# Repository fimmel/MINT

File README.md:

# MINT Access Control System

This is the custom system for Access and tool control for the Rutland MINT makerspace. It uses standard HID readers, Arduinos, and a backend SQL database with a PHP webserver to manage users, permission, and cards.

There is lotsmore coming as well as an overview of how it all works

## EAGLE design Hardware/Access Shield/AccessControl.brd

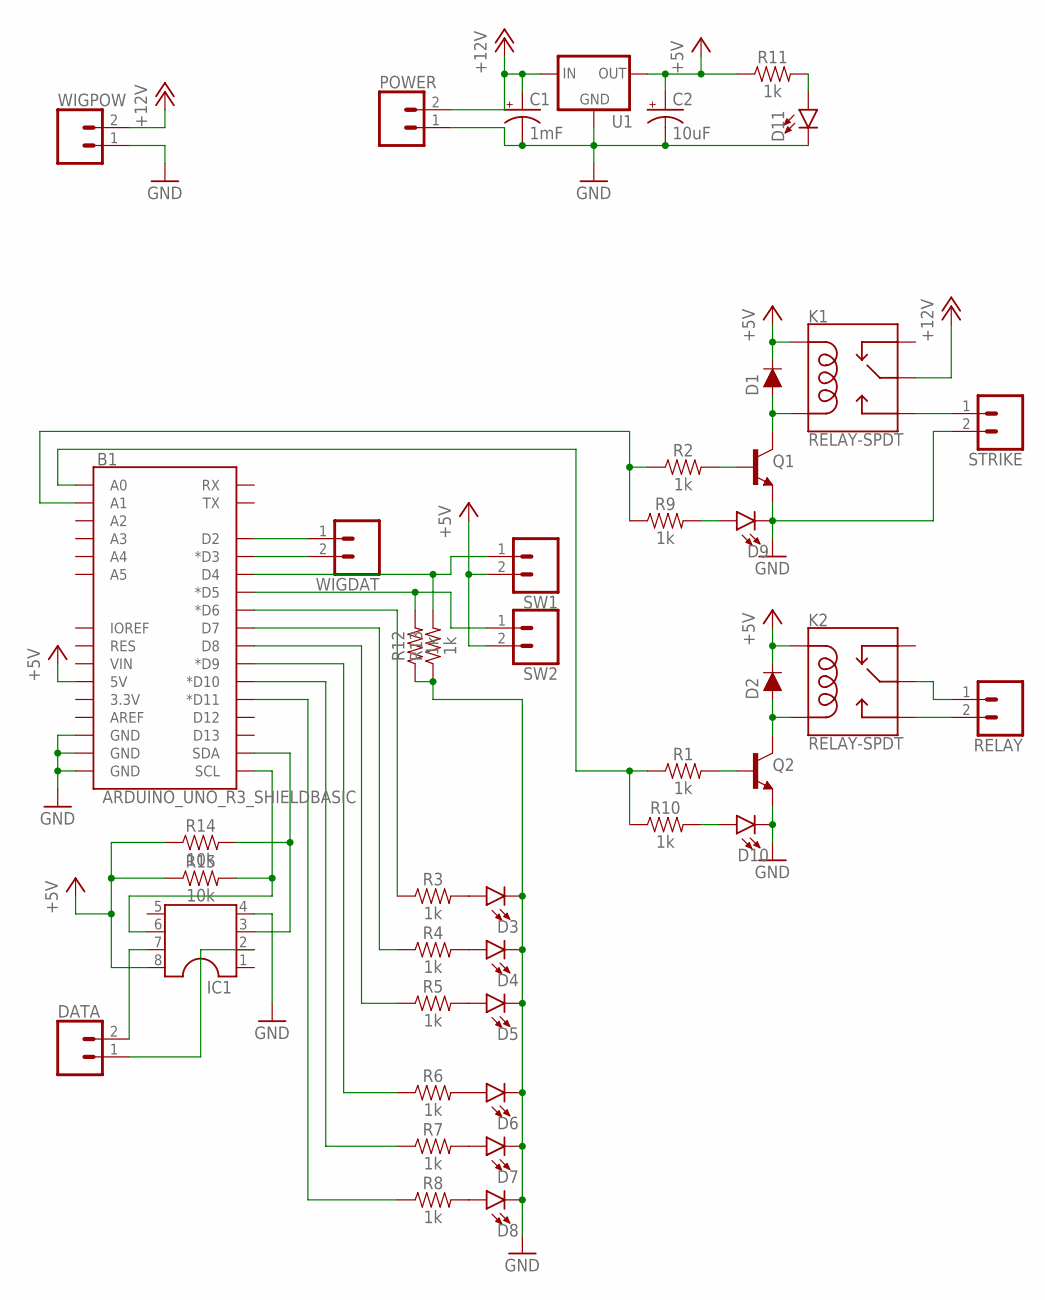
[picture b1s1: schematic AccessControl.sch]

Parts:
B1: ARDUINO_UNO_R3_SHIELDBASIC; UNO_R3_SHIELD
C1: 1mF; CPOL-RADIAL-5MM-10MM
C2: 10uF; CPOL-RADIAL-2.5MM-5MM
D1, D2: DIODE-KIT2; DIODE-1N4001-KIT
D3, D4, D5, D6, D7, D8, D9, D10, D11: LED5MM; LED_5MM
DATA: CONN_025MM; SCREWTERMINAL-5MM-2
IC1: DIL8; DIL08
K1, K2: RELAY-SPDT; RELAY-JZC
POWER: CONN_025MM; SCREWTERMINAL-5MM-2
Q1, Q2: TRANS_NPN-P2N2222A; TO-92
R1, R2, R3, R4, R5, R6, R7, R8, R9, R10, R11, R12, R13: 1k; AXIAL-0.1
R14, R15: 10k; AXIAL-0.1
RELAY: CONN_025MM; SCREWTERMINAL-5MM-2
STRIKE: CONN_025MM; SCREWTERMINAL-5MM-2
SW1, SW2: CONN_025MM; SCREWTERMINAL-5MM-2
U1: V_REG_78XXSINK; TO220-IGO
WIGDAT: CONN_025MM; SCREWTERMINAL-5MM-2
WIGPOW: CONN_025MM; SCREWTERMINAL-5MM-2

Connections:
+5V: B1.5V, C2.1 (+), D1.C, D2.C, IC1.8, K1.5 (COIL1), K2.5 (COIL1), R11.P$1 (1), R14.P$1 (1), R15.P$1 (1), SW1.2, SW2.2, U1.OUT
+12V: C1.+, K1.4 (MAIN), POWER.2, U1.IN, WIGPOW.2
GND: B1.GND@0 (GND), B1.GND@1 (GND), B1.GND@2 (GND), C1.-, C2.2 (-), D3.K (C), D4.K (C), D5.K (C), D6.K (C), D7.K (C), D8.K (C), D9.K (C), D10.K (C), D11.K (C), IC1.4, POWER.1, Q1.3 (E), Q2.3 (E), R12.P$1 (1), R13.P$1 (1), STRIKE.2, U1.GND, WIGPOW.1
unnamed: D1.A, K1.1 (COIL2), Q1.1 (C)
unnamed: Q1.2 (B), R2.P$2 (2)
unnamed: D2.A, K2.1 (COIL2), Q2.1 (C)
unnamed: Q2.2 (B), R1.P$2 (2)
unnamed: K2.3 (NO), RELAY.2
unnamed: K2.4 (MAIN), RELAY.1
unnamed: K1.3 (NO), STRIKE.1
unnamed: B1.D2, WIGDAT.1
unnamed: B1.D3 (*D3), WIGDAT.2
unnamed: B1.A0, R1.P$1 (1), R10.P$1 (1)
unnamed: B1.A1, R2.P$1 (1), R9.P$1 (1)
unnamed: D3.A, R3.P$2 (2)
unnamed: D4.A, R4.P$2 (2)
unnamed: D5.A, R5.P$2 (2)
unnamed: D6.A, R6.P$2 (2)
unnamed: D7.A, R7.P$2 (2)
unnamed: D8.A, R8.P$2 (2)
unnamed: D11.A, R11.P$2 (2)
unnamed: D9.A, R9.P$2 (2)
unnamed: D10.A, R10.P$2 (2)
unnamed: B1.D6 (*D6), R3.P$1 (1)
unnamed: B1.D7, R4.P$1 (1)
unnamed: B1.D8, R5.P$1 (1)
unnamed: B1.D9 (*D9), R6.P$1 (1)
unnamed: B1.D10 (*D10), R7.P$1 (1)
unnamed: B1.D11 (*D11), R8.P$1 (1)
unnamed: B1.SDA, IC1.3, R14.P$2 (2)
unnamed: B1.D4, R13.P$2 (2), SW1.1
unnamed: B1.D5 (*D5), R12.P$2 (2), SW2.1
unnamed: B1.SCL, IC1.6, R15.P$2 (2)
unnamed: DATA.2, IC1.7
unnamed: DATA.1, IC1.2

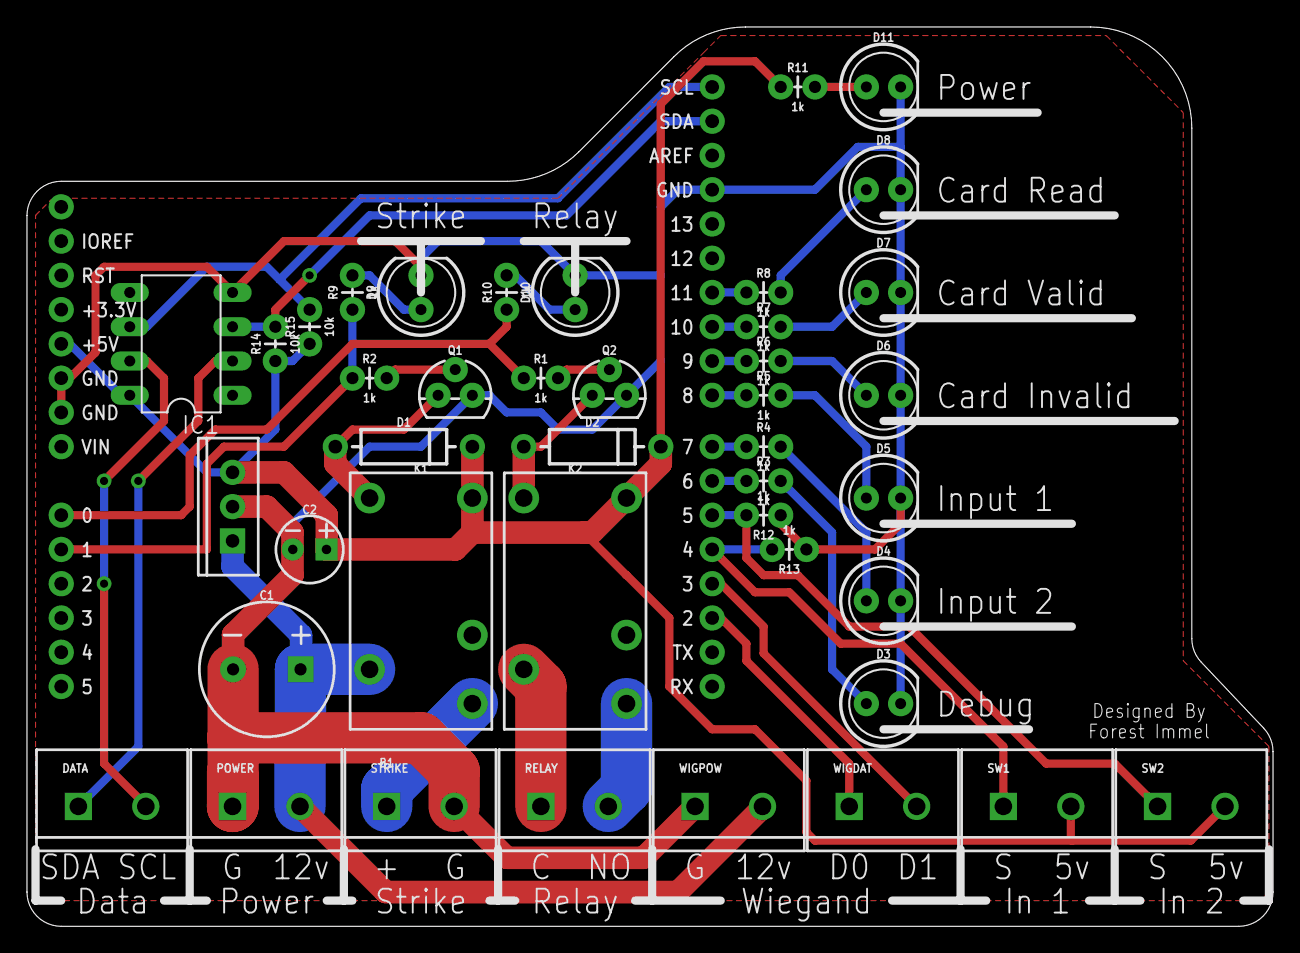
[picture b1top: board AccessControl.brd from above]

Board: 2 copper layers, 92.4 x 66.7 mm, 43 parts (0 on the bottom side), 35 nets.

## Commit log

2017-07-12 Rev 1 of the Arduino Shield
    The first round of production boards as well as some photos
2017-07-12 Initial Commit of arduino code for the door reader
    This is for the arduino that uses the shield and talks to the HID reader and uses i2c to the master to validate cards

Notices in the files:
parts and their libraries:
SparkFun-Boards: Licensing: Creative Commons ShareAlike 4.0 International - https://creativecommons.org/licenses/by-sa/4.0
